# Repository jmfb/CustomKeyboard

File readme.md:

# Custom Keyboards

## V1

I took a prefabricated tenkeyless PCB and used a dremel to cut it into 3 pieces:
- Left hand board (jagged cut at F5, 6, T, G, B)
- Right hand board (jagged cut at F6, 7, Y, H, N)
- Arrow keys

I proceeded to use the dremel to sever all PCB traces for the keys but left the diode traces.
Cherry MX brown switches were then directly mounted to the PCB.  Note that these switches were
the ones designed to be plate mounted (did not include the extra two plastic pegs for direct PCB mounting) so the keys ended up looking crooked.

The switches were then wired into the standard row/column matrix and wires were all routed through to an external Teensy2.0 controller.  2x5 and 2x3 headers were used for the connecting cables.  The keycaps were a standard profile blank set.

The next phase was designing a custom PCB for the number pad (to "complete" the full keyboard) and testing out both 3D printed and lasercut mounting plates.

### Lessons Learned

- Direct PCB mounting was crooked (at least using the non-PCB mount keys).
- Lasercut acrylic mounting plates were sturdier, cheaper, and looked cooler than the 3D printed versions.
- Arrow keys and number pad could be combined into a single board.
- Blank keycaps were difficult to use (I guess I still occasionally look).
- The placement of the right hand spacebar required the right thumb to tuck.
- The external controller for the Teensy and the external cable management boards made for too many components.
- The keys come with holes for LEDs that I might as well be using.
- A wristpad was necessary to use the keyboard and would nice if it were affixed.

## V2

I designed 3 custom PCBs using KiCad:
- Left hand board (capslock key replaced with Teensy2.0 controller)
- Right hand board
- Accessory board (arrows and numbpad)

I designed lasercut mounting plates using OpenSCAD.

I upgraded to using Cherry MX blue switches and double shot DCS keycaps and installed green LEDs on each key.

I extended the base plate to make room to glue wristpads onto the boards.

### Lessons Learned

- Direct soldering of the LEDs to the PCB made it difficult to replace them when they loosened or burned out.
- The double shot keycaps felt great but didn't allow for the LED light to show through.  Translucent keycaps would have been better.
- A better solution than just gluing the PCB to a board would be needed for a case (someting that could be assembled/disassembled, and that had walls).

## V3

This design used the same PCBs and mounting plates as V2.

Cherry MX green switches were used.  After using a sampler board with several types of switches I thought the ultra stiff key would be awesome.

Lasercut faceplates, lasercut baseplates, and 3D printed case walls were designed using OpenSCAD.  Three versions of the case walls were printed to test out different materials and different 3D printing vendors: i.Materialise, Sculpteo, and Shapeways.

SIP LED sockets were put into each of the key switches to allow for the LEDs to be replaced.  A mix of blue and green LEDs were used (blue for control keys).

Doubleshot translucent keycaps were used to allow for the LED light to show through.

The controller logic was updated to make the left hand space be a hyper key.

### Lessons Learned

- The 3D walls designed for the case were too tight of a fit and bowed out.  It made for a sturdy design but required too precise measurements for a perfect fit.  The next case should use screws/standoffs to mount the PCB vs. grooved walls.
- 3D printing was too expensive and slow compared to laser cutting.  The next case should be made solely from lasercut parts.
- The hyper key functionality was great, but I occassionally missed having the left hand spacebar.  More keys next time.
- The 2x5/2x3 connector cables looked unprofessional (probably because of the rainbow colored cables).
- I measured the baseplates based on the previous wristpad size and when I couldn't reorder the same type of wristpad had to use bigger ones that hung over the edge of the baseplates.  Obtain wristpads prior to measuring baseplates.
- The cutoff edge of the wristpads looked unprofessional.
- After double checking the PCB and laser cutting capabilities there is no need to keep the accessory board separate.
- Stabilizers for the 2+ keys would be nice.  Need to update PCB for holes, mounting plates for holes, and move PCB components in the way of the footprints.
- Not sure how I feel about the green switches.  I like the stiff feel but I don't think I love them like I did the blues.
- The LEDs were mounted on the bottom of the keys but the translucent keycaps were designed to shine through the top.  Will need to flip key switches to optimize translucent effects of the keycaps.  Note that vertical keys should have LEDs to the left.
- The key spacing for larger unit keys (1.25, 1.5, 1.75, 2, 2.25, and 2.75) had been using measured positions and worked.  However, when attempting to make a perfect rectangle for each hand it was discovered that 19mm * keysize was needed to prevent 1mm error for several rows.  This increased resolution for key spacing to 1/8th mm from 1/2 mm.

## V4

3 new PCBs were designed using KiCad:
- Extended left hand board (include arrow keys and slightly inverted numpad to mirror right hand board).
- Extended right hand board (combined right hand board and accessory board).
- External connector board (houses Teensy and 2 25-pin D-sub connectors).

The left hand board had arrow keys added to the left of the previous left edge.  A numpad was added to the left of that but with the outside edge of keys mirrored and the zero and period flipped.  The mirroring was so the enter would still be hit with the pinky and the zero still with the thumb.  The numbers were not flipped because I didn't want to retrain my brain for my left hand.  Above the numpad, four programmable buttons were added (N1-4, sometimes used for volume controls or extended operators for the numpad).  To the left of the numpad a vertical row of programmable buttons was added (M1-6, as part of the more keys strategy) that used some of the gaps in the row/column matrix.  To the right of the jagged edge, a vertical row of programmable keys was added (L1-6) and different sized keys were used to make the board a perfect rectangle.  A new hyper key (LEFT_HYPER) was also added to the left of the spacebar to fill in the gap between alt and the spacebar.  The capslock key was re-added since the Teensy is being moved onto its own board (whether this gets remapped is programmable).  The main part of this board is 8.5 standard keys wide.

The right hand board was combined with the previous accessory board.  The same jagged gap was filled on this board to make it a perfect rectangle though one more key was added (two keys were added to the left of the function key row) for an additional 7 keys (R1-7).  A new hyper key was added to the right of the spacebar (RIGHT_HYPER) and the right windows key was re-added (previously just had the right menu key between alt and ctrl).  The same N1-4 and M1-6 keys were also added to this board (note they are not independently programmable because they map to the same row/column scan position).  The main part of this board is 10 standard keys wide.

The full keyboard contains 170 keys; 130 distinct row/column scan positions.  Note that there are still 2 unused row/scan positions in the 12x11 row/scan matrix.  There wasn't anywhere convenient left to put them though.

A single 25-pin D-sub connector exists on each board. 12 row pins, 11 column pins, VCC, and GND (for LEDs).  Instead of chaining the left board to the right board and having the USB cable and connector cable on the left board, the Teensy was moved off onto a controller board.  The controller board just maps the Teensy pins to 2 D-sub connectors (one for the left hand board and one for the right hand board, with both cables having the same pin assignments).

The case design was switched to use all lasercut pieces.  The walls are notched together and slide pegs into the baseplate and faceplate.  A 3mm overhang, 3mm wall depth, and 1mm spacing between wall and PCB makes each dimension of the base/face 14mm longer than the PCB/mounting plate sizes.  Screw holes are drilled into the border and one near the arrow keys for some center support.  M2 screws (5mm male end), 0.5mm washers, 5mm M/F standoffs (3mm wide with 4mm male end), and 8mm F/F standoffs (3mm wide) are used to affix the PCB to the base and affix the faceplate to the walls.  From the bottom, it goes: screw, base, 5mm M/F standoff, PCB, washer, 8mm F/F standoff (though hole for mounting plate), 2 washers, faceplate, washer, screw.

All case parts for all three boards can be combined into a single CAD file and lasercut from two P3 pieces from Ponoko (one for the baseplates and walls and one for the mounting plates and faceplates).  Since there was space for two connector faceplates, I decided to make one with a little bit of artwork and cut out a flux capacitor.  Because if you're going to build your own keyboard why not build one with style!

Cherry PCB mounted stabilizers were added.  Two sets of translucent keycaps were needs due to the number of additional keys.

### Lessons Learned

- D-Sub connector height measurement was imprecise and pushed the faceplate up about 1mm.  Filing it down took part of the edge off, but using a micrometer will yield better wall/faceplate height measurements.
- Using the washers on the screw/standoff connections was impractical due to the small size of the washers, the inconvenient location of the screws (near walls or central to the board and under the mounting plate).  The screw/standoff premise is solid though and made a very sturdy and professional looking case.
- The location of the D-Sub connectors on the boards was inconvenient for placement near monitors.  I think the outside edge would make the most sense for the next version.
- More keys was a bad idea.  The inner row keys ended up getting pressed by accident too often and ruined the tactile feel for finding my position on the keyboard without looking.  While there was potential for adding useful keys (left hand enter, backspace, right hand tab, escape) the opposite was experienced.  The extra left hand board made it difficult to find home for my left hand (naturally always seeking leftmost position).  The extra numpad and outer macro keys filled out the keyboard but were too out of the way to add anything useful to them (it was more burdensome to try to figure out what to assign to the keys).  I am not sure about how I feel about the hyper key near the spacebar because of the other things that made typing difficult.  I do still think a hyperkey or two is a good idea.
- The offboard teensy and extra cabling has the benefit of keeping a single cable going to each board but uncovered a problem with wiring resistance that was solved with a delay in the controller logic during rowscan to allow the signals in the lines to stabilize (which was taking at least one extra clock cycle and causing phantom keypresses in the first two columns of the scan matrix).
- I didn't glue down the wristpad on this one because I was tired of buying more and more wristpads.  However, they slip around too much otherwise.  They need to be fixed to the keyboard case.  Sewing the edge flap down did make them look much better than the glued end of cut off end.
- I think the Cherry MX Green switches were cool for a while but in the end not as nice to type on.  Going back to the blue switches from V2 felt amazingly good by comparison.
- The mix of blue and green LEDs was kind of cool but I don't love it.  I think short of RGB LEDs I will stick with a single color.  Probably green but blue was fine too.  The SIP sockets rock.
- Having the CapsLock key back was a mistake - definitely never use it and every time it is pressed was an accidental hit.  I might leave it off next time.  Would the overall look suffer though?
- The flux capacitor design in the connector board was basically invisible because of the clear faceplate.  However, the top leg did provide a hole through to the teensy reset button which came in handy.  Might just keep that hole.
- The cherry stabilizers worked out great.  Clean fit into PCB, perfect cutout for mounting plate.  There was one resistor that was close to a support bar.
- Pro-tip: prior to soldering the keys onto the PCB make sure all key pins went through.  One pin had bent down and I didn't discover it until half of the keys were soldered.  That meant I was almost fucked.  I ended up shoving a bit of wire through the hole and drenching it in solder hoping that surface tension would pull enough solder down the wire to make the connection to the bent pin.  It worked, but had it not I don't know what I would have done.
- A few more screws in certain locations would make the faceplate more stable (at least on the right hand board).

## V5

### Left Hand

- Getting rid of left hand accessory board (arrows and numpad).
- Getting rid of outside column macro keys (M1-6) and inside column macro keys (L1-6).
- Removing the caps lock key.  Could have left it for looks and mapped it to a hyper key or something, but not worth the mistakes.
- Keeping the left hyper key.
- Moving D-Sub connector to left edge at the top.
- Using a total of 7 screw holes to build case.
- Total of 35 keys (2 2+ keys) with max row width being 7.5 keys (bottom row).

### Right Hand

- Getting rid of outside column macro keys (M1-6) and inside column macro keys (R1-7).
- Keeping numpad macro keys (N1-4).
- Keeping right hyper key and right windows key.
- Moving D-Sub connector to right edge at the top.
- Using a total of 15 screw holes to build case.
- Total of 75 keys (7 2+ keys) with max row width being 9 keys (bottom row, excluding accessory keys).

### Connector Board

- Reusing design from V4.  Will be able to use the same PCB.
- Leaving a hole in the faceplate for the Teensy reset button.
- Using a total of 4 screw holes to build case.

### General Updates

- Fixing case wall height to take into account micrometer measurements for D-Sub connectors (10.3mm vs. previous measurement of 9.5mm).
- Using 10mm F/F standoffs to connect PCB to faceplate (a 0.3mm gap will exist, should be fine).
- Not using washers in any part of screw assembly (too small and can't get in most spots).
- Using same color LED for all keys (green).
- Going back to Cherry MX Blue switches.
- Plan on getting custom DCS row 6 keycaps for hyper keys (left is 1.5, right is 1.75) and space keys (both 2.25).

### Lessons Learned

- This keyboard is just plain awesome.
- Right hand board is still very large and is sometimes awkward to fit onto desk near monitors.
- Large right hand board occasionally gets wobble when crossing desk boundaries.
- Very minor use of hyper keys due to completely normal keyboard layout.
- N1-4 keys are never used (and completely out of the way).
- Uses 3 2.25 keys (left shift and both spacebars) which makes complete keycap sets difficult.
- Using unused capslock as right hyper is perfect.
- Still do not miss the capslock key (nor do I wish there were a key there I could hit).
- Single color keyboard is okay (looks neat but not awesome).  Have built both a green and blue version.
- Ran out of blue switches for second one and used green for function keys - don't even notice because of how rarely they are used.
- D-sub cables give a classic/punk look to the keyboard but are a bit large (bump into monitors still, even on the outside top).
- Cost for materials (case/PCB) is higher than ideal due to large right hand board.
- Connector board is larger than it needs to be.

## Mini V1

### Goals

- Build a miniature keyboard (40%-like) and use hyper-functionality to improve current coding workflows.
- Have an easy to hit underscore (for snake casing, lambdas, garbage identifier prefixes, etc.).
- Reduce PCB/case material costs (just in case I want two of them again!).
- Have smaller and more hidden cables connecting the boards (keep off-board controller for symmetry).
- Columnar layout (will definitely need to re-learn typing).
- Minimal "reach" keys (1 row up, 1 row down, 1 row over to either side).
- Rely on thumb buttons for extra keys (no clue what layout yet).
- RGB LEDs so I can have that awesome feel of dynamic color and responsive changes.

### Parts, Prices, and Datasheets

- Cherry MX Blue RGB PCB Mount Switches (x23 x2)
	- MX1A-EN1B (NOTE: Only wanted MX1A-EN1A, plate mounted, but were constantly out of stock)
	- [Blue Datasheet](https://www.cherrymx.de/_Resources/Persistent/a531cb6598bc849cbcf131fd7a31814282b74545/EN_CHERRY_MX_BLUE.pdf)
	- [Footprint Datasheet](https://cdn.sparkfun.com/datasheets/Components/Switches/MX%20Series.pdf)
	- [LED Cutout Datasheet](https://drive.google.com/file/d/0B5JcED9YINdnNU1qajJmVmtEcUU/view?resourcekey=0-LZfcyjo3jcX8JEKJD6tRKA)
	- [MechanicalKeyboards](https://mechanicalkeyboards.com/shop/index.php?l=product_detail&p=4451)
	- $0.50 / switch @ 100 = $50.00 (bulk discount)
- Pin Receptacle Connector (Maybe, adds height to key and might throw off 3mm spacing between PCB and mounting plate)
	- 0305-2-15-15-47-27-10-0 (ED90333-ND)
	- [Datasheet](https://www.mill-max.com/products/datasheet/pinsrecs/0305-2-15-80-47-80-10-0)
	- [Digikey](https://www.digikey.com/en/products/detail/mill-max-manufacturing-corp/0305-2-15-15-47-27-10-0/1801940)
	- $0.22906 / connector @ 200 = $45.81 (bulk discount, went in on 500 with Greg).
- Keyswitch Diode (x23 x2)
	- 1N4148 (1N4148FS-ND)
	- [Datasheet](https://rocelec.widen.net/view/pdf/bhc41r7lwc/ONSM-S-A0003539415-1.pdf?t.download=true&u=5oefqw)
	- [Digikey](https://www.digikey.com/en/products/detail/on-semiconductor/1N4148/458603?s=N4IgTCBcDaIIwDkAsckA4BiBlAtAgIiALoC%2BQA)
	- $0.01622 / diode @ 1000 = $16.22 (bulk discount)
- RGB LED with IC (x23 x2)
	- APA102C (iPixel LED)
	- [Datasheet](https://cdn.sparkfun.com/datasheets/Components/LED/APA102C.pdf)
	- [Sparkfun](https://www.sparkfun.com/products/16345)
	- $0.379 / LED @ 50 = $18.95
- 9pin Mini-DIM Female Connector, Through Hole, Right Angle (x1 x2 + connector x2)
	- MD-90S (CP-2490-ND)
	- [Datasheet](https://www.cuidevices.com/product/resource/md-s.pdf)
	- [Digikey](https://www.digikey.com/en/products/detail/cui-devices/MD-90S/145320)
	- $2.95 / connector @ 4 = $10.80
- 9pin Mini-DIM Male/Make 3ft. Cable (x2)
	- MD9MM3BLK
	- [Datasheet](https://www.kraydad.com/mini-din-9-pin-b-type-cables/)
	- [Kraydad](https://www.kraydad.com/mini-din-9-pin-b-type-3-ft-male-to-male-black-cable/)
	- $12.49 / cable @ 2 = $24.98
- Cherry PCB Snap-in Stabilizers (2u x2 x2)
	- 60%/TKL (NOTE: includes 5 2u wires, only need 4)
	- [Amazon](https://www.amazon.com/Genuine-Cherry-PCB-Snap-Stabilizers/dp/B085T8QZJC)
	- $14.99 / pack @ 1 = $14.99
- M4 Hex Brass F/M Standoff 18mm/6mm w/ Screw and Nut (x4 x2)
	- Set of 20 (need 4 or 5 per board)
	- [Amazon](https://www.amazon.com/gp/product/B08ZXSR7MP)
	- $0.5745 / set @ 20 = $11.49
- M4 Brass Washer 9mm OD, 4.3mm ID, 0.8mm Thick (x4 x2)
	- Pack of 100 (need 4 or 5 per board)
	- [Amazon](https://www.amazon.com/gp/product/B009OK2KPU)
	- $0.0827 / washer @ 100 = $8.27
- M2 Brass F/M Standoff 5mm/4mm
	- Pack of 100 (need 4 for controller)
	- [Amazon](https://www.amazon.com/gp/product/B00REFG0TE/ref=ppx_yo_dt_b_search_asin_title?ie=UTF8&psc=1)
	- $0.0949 / standoff @ 100 = $9.49
- M2 Brass F/F Standoff 8mm (first controller)
	- Pack of 50 (need 4 for controller)
	- [Amazon](https://www.amazon.com/gp/product/B00BWLQYRY/ref=ppx_yo_dt_b_search_asin_title?ie=UTF8&psc=1)
	- $0.226 / standoff @ 50 = $11.30
- M2 Brass F/F Standoff 10mm (second controller)
	- Pack of 100 (need 4 for controller)
	- [Rakuten](https://www.rakuten.com/shop/unique-bargains/product/a14081400ux0120/)
	- $0.0683 / standoff @ 100 = $6.83
- M2 5mm Screws
	- Pack of 60 (need 8 for controller)
	- [Amazon](https://www.amazon.com/gp/product/B013T1U4LG/ref=ppx_yo_dt_b_search_asin_title?ie=UTF8&psc=1)
	- $0.1195 / screw @ 60 = $7.17
- Clear Soft Close Drawer Cabinet Door Bumpers (x6 x2 + connector x4)
	- 9.5mm x 3.8mm, 72pc sheet
	- [Amazon](https://www.amazon.com/dp/B06XCGM8JT)
	- $0.0968 / bumper @ 72 = $6.97
- Mini USB A to Mini-B Cable, Black, 3ft (x1)
	- 103896 (any Mini USB cable will do if you already have one)
	- [Amazon](https://www.amazon.com/Monoprice-3-Feet-mini-B-28AWG-103896/dp/B003L18SHC)
	- $5.23 / cable @ 1 = $5.23
- Teensy 2.0 (x1)
	- No pins
	- [Datasheet](https://www.pjrc.com/store/teensy.html)
	- [Amazon](https://www.amazon.com/gp/product/B00NC43256)
	- $18.75 / chip @ 1 = $18.75 ($16 from PJRC but with shipping)
	- NOTE: Plans to discontinue this model in 2022; recommend switching to 32-bit boards.
- Header Pins (x12 x2, though more pins available on Teensy)
	- Breakaway header, straight, brass
	- [Sparkfun](https://www.sparkfun.com/products/116)
	- $1.50 / 40pin strip @ 1 = $1.50
	- NOTE: Larger volumes and lower per-pin cost are on amazon but not brass pins
- Demultiplexer, 3:8 (x1 x2)
	- SN74HC138N (296-1575-5-ND)
	- [Datasheet](https://www.ti.com/lit/ds/scls107f/scls107f.pdf)
	- [Digikey](https://www.digikey.com/en/products/detail/texas-instruments/SN74HC138N/277221)
	- $0.461 / chip @ 10 = $4.61 (bulk discount)
- Parallel Load, Shift Register (x1 x2)
	- SN74HC165N (296-8251-5-ND)
	- [Datasheet](https://www.ti.com/lit/ds/symlink/sn74hc165.pdf)
	- [Digikey](https://www.digikey.com/en/products/detail/texas-instruments/SN74HC165N/376966)
	- $0.525 / chip @ 10 = $5.25 (bulk discount)
- 10kOhm Pullup Resistors (x8 x2)
	- CF18JT10K0 (CF18JT10K0CT-ND - Cut Tape (CT))
	- [Datasheet](https://www.seielect.com/catalog/sei-cf_cfm.pdf)
	- [Digikey](https://www.digikey.com/en/products/detail/stackpole-electronics-inc/CF18JT10K0/1741566)
	- $0.01116 / resistor @ 500 = $5.58 (bulk discount)
- Wristpad (x1 x2, but both cut from 1)
	- Glorious Gaming Write Pad, Standard Size
	- [Amazon](https://www.amazon.com/Glorious-Gaming-Wrist-Pad-Rest/dp/B00V5AXPTW)
	- $26.99 / pad @ 1 = $26.99
- Doubleshot Translucent Pudding Keycaps (x15 x2)
	- Standard Set
	- [Amazon](https://www.amazon.com/gp/product/B09241HV9H)
	- $19.99 / set @ 1 = $19.99
- DCS Clear Keycaps (x8 x2)
	- 1u R2 x2, 1u R3 x2, 1u R4 x8, 2u R3/4 x4
	- [Datasheet](https://pimpmykeyboard.com/template/images/DCSFamily.pdf)
	- [PimpMyKeyboard](https://pimpmykeyboard.com/dcs-clear-keys-and-key-sets/)
	- $1.00 / 1u @ 12 = $12.00
	- $1.50 / 2u @ 4 = $6.00
- Laser Cut Parts
	- [Ponoko](https://www.ponoko.com)
	- All 3mm parts are Green Translucent Acrylic
	- All 1.5mm parts are Clear Acrylic (not available in Green Translucent)
	- Controller (3mm) $7.69 @ 1 = $7.69
	- Base Plate (3mm) $7.15 @ 2 = $14.30
	- Mounting Plate (1.5mm) $7.71 @ 2 = $15.42
	- Lower Layer (3mm) $5.965 @ 4 = $23.86
	- Upper Layer (3mm) $6.08 @ 2 = $12.16
	- Face Plate (3mm) $3.855 @ 4 = $15.42
	- Face Plate (1.5mm) $2.815 @ 2 = $5.63
	- Multi-product discount $30.91
	- Setup Fee $14.00
	- Total: $77.57
- PCB
	- [Seeed Studio](https://www.seeedstudio.com)
	- Controller $0.98 @ 5 = $4.90
	- Left Hand $6.486 @ 5 = $32.43
	- Right Hand $6.486 @ 5 = $32.43
	- Shipping (DHL from China) $30.19
	- Total: $19.99 @ 5 = $99.95
- Total cost of parts for a single keyboard: $313.34

### Lessons Learned

- Fitting 5x5mm LEDs not a perfect fit (could have made a tad wider for flush fit; would also fit rounded PCB cut corner issue too)
- Soldering LEDs difficult.  Not sure what to do about this other than magnifying glass w/ light.
- Chaining VCC/GND may have been a poor choice, still not sure.  Definitely problematic when attempting to remove an LED.
- Socketing switches seems like a good idea (reduce switch cost for multiple prototypes, allow replacing switches in long-lived versions).  However, increases distance between mounting plate and PCB by ~1mm.  I think I can take that out on pegs.
- With the surface mount pegs, the mounting plate does seem a little bit redundant.  Eliminating the mounting plate and the 1.5mm faceplate layer would reduce overall height by 3mm (shorter M4 scews) and allow for a completely 3mm layer construction.
- Controller board; teensy height from PCB is slightly greater than the 8mm F/F standoffs (not sure how I missed that).  Damn, old controller used 10mm F/F standoff.
- Well, it puts the previous lessons to shame, but the controller "lid" didn't go deep enough with the connector cutouts!  Missed "PCB spacing, wall depth, overhang" padding and just did connector size.
- Tab being lower for the pinky takes getting used to (hit escape a lot).
- Only using bottom half of 2-keys.  Possibly simplify down to 1u size?
- Sometimes hit Win instead of Ctrl when reaching with thumb.  Could stagger keys for thumb; possibly get rid of one of grid keys and just have left hand Win and right hand Menu (or no Menu, I mean who uses that key?)
- Had a few iterations of controller software.  Unit tests for expected key reports were vital (lots of bugs found that way and prevent breaking changes in the future).

## Mini V2

### Goals

- Fix LED hole size to make assembly and soldering easier.
	- Move cutout to keyswitch footprint (manually in file if IDE does not support it).
	- Increase width of cutout to allow surface mount leads to fit inside PCB.
	- Also increase width of peg cutout to account for rounded PCB cutout.
- Fix all incorrect case measurements.
	- 10mm standoffs for controller top.
	- Fix controller lid cutouts for connectors.
	- Reduce peg inner height by 1mm to account for keyswitch sockets.
	- Adjust connector cutout (rubs on bottom).
	- Add holes for demux and register to mounting plate.
- Add hardware support for right or left hand detection.
	- Hardwire first two register pins to 01 for left and 10 for right.  11 indicates disconnected.
	- Software detection to read keyscan and switch LED output.

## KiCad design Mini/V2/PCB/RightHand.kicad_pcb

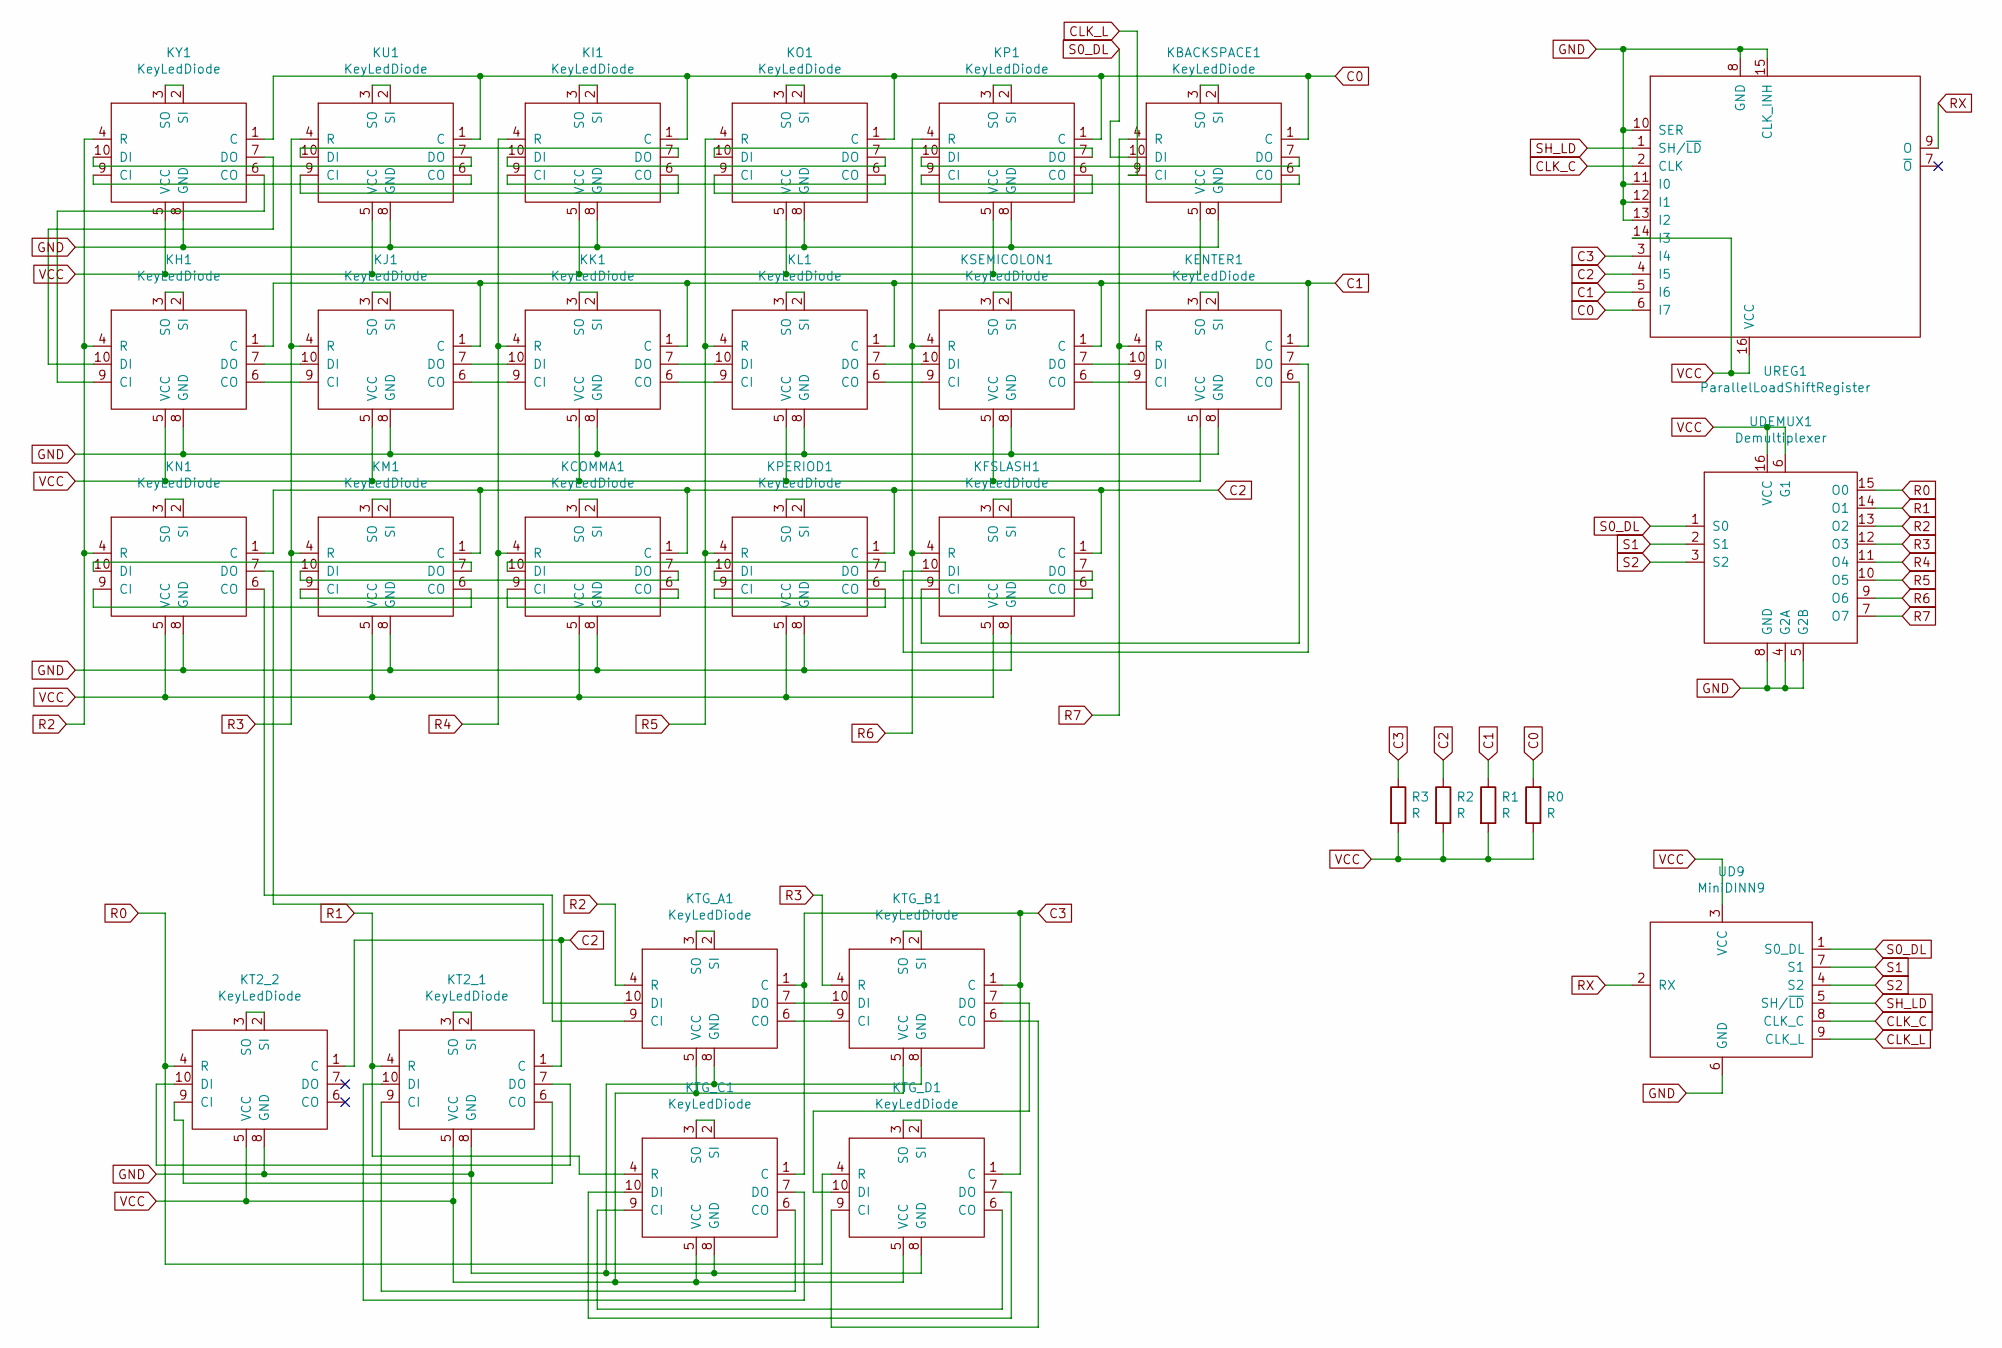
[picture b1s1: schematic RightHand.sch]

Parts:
KBACKSPACE1: KeyLedDiode; KeyLedDiodeR2L
KCOMMA1: KeyLedDiode; KeyLedDiodeR2L
KENTER1: KeyLedDiode; KeyLedDiodeL2R
KFSLASH1: KeyLedDiode; KeyLedDiodeR2L
KH1: KeyLedDiode; KeyLedDiodeL2R
KI1: KeyLedDiode; KeyLedDiodeR2L
KJ1: KeyLedDiode; KeyLedDiodeL2R
KK1: KeyLedDiode; KeyLedDiodeL2R
KL1: KeyLedDiode; KeyLedDiodeL2R
KM1: KeyLedDiode; KeyLedDiodeR2L
KN1: KeyLedDiode; KeyLedDiodeR2L
KO1: KeyLedDiode; KeyLedDiodeR2L
KP1: KeyLedDiode; KeyLedDiodeR2L
KPERIOD1: KeyLedDiode; KeyLedDiodeR2L
KSEMICOLON1: KeyLedDiode; KeyLedDiodeL2R
KT2_1: KeyLedDiode; Key2LedDiodeL2R
KT2_2: KeyLedDiode; Key2LedDiodeR2L
KTG_A1: KeyLedDiode; KeyLedDiodeL2R
KTG_B1: KeyLedDiode; KeyLedDiodeL2R
KTG_C1: KeyLedDiode; KeyLedDiodeR2L
KTG_D1: KeyLedDiode; KeyLedDiodeR2L
KU1: KeyLedDiode; KeyLedDiodeR2L
KY1: KeyLedDiode; KeyLedDiodeR2L
R0, R1, R2, R3: R; PullupResistor
UD9: MiniDINN9; MiniDin9
UDEMUX1: Demultiplexer; DualInlineMicrochip2x8
UREG1: ParallelLoadShiftRegister; DualInlineMicrochip2x8

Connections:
C0: KBACKSPACE1.1 (C), KI1.1 (C), KO1.1 (C), KP1.1 (C), KU1.1 (C), KY1.1 (C), R0.2, UREG1.6 (I7)
C1: KENTER1.1 (C), KH1.1 (C), KJ1.1 (C), KK1.1 (C), KL1.1 (C), KSEMICOLON1.1 (C), R1.1, UREG1.5 (I6)
C2: KCOMMA1.1 (C), KFSLASH1.1 (C), KM1.1 (C), KN1.1 (C), KPERIOD1.1 (C), KT2_1.1 (C), KT2_2.1 (C), R2.1, UREG1.4 (I5)
C3: KTG_A1.1 (C), KTG_B1.1 (C), KTG_C1.1 (C), KTG_D1.1 (C), R3.1, UREG1.3 (I4)
CLK_C: UD9.8 (CLK_C), UREG1.2 (CLK)
CLK_L: KBACKSPACE1.9 (CI), UD9.9 (CLK_L)
GND: KBACKSPACE1.8 (GND), KCOMMA1.8 (GND), KENTER1.8 (GND), KFSLASH1.8 (GND), KH1.8 (GND), KI1.8 (GND), KJ1.8 (GND), KK1.8 (GND), KL1.8 (GND), KM1.8 (GND), KN1.8 (GND), KO1.8 (GND), KP1.8 (GND), KPERIOD1.8 (GND), KSEMICOLON1.8 (GND), KT2_1.8 (GND), KT2_2.8 (GND), KTG_A1.8 (GND), KTG_B1.8 (GND), KTG_C1.8 (GND), KTG_D1.8 (GND), KU1.8 (GND), KY1.8 (GND), UD9.6 (GND), UDEMUX1.4 (G2A), UDEMUX1.5 (G2B), UDEMUX1.8 (GND), UREG1.8 (GND), UREG1.10 (SER), UREG1.11 (I0), UREG1.12 (I1), UREG1.13 (I2), UREG1.15 (CLK_INH)
unnamed: KBACKSPACE1.2 (SI), KBACKSPACE1.3 (SO)
unnamed: KBACKSPACE1.6 (CO), KP1.9 (CI)
unnamed: KBACKSPACE1.7 (DO), KP1.10 (DI)
unnamed: KCOMMA1.2 (SI), KCOMMA1.3 (SO)
unnamed: KCOMMA1.6 (CO), KM1.9 (CI)
unnamed: KCOMMA1.7 (DO), KM1.10 (DI)
unnamed: KCOMMA1.9 (CI), KPERIOD1.6 (CO)
unnamed: KCOMMA1.10 (DI), KPERIOD1.7 (DO)
unnamed: KENTER1.2 (SI), KENTER1.3 (SO)
unnamed: KENTER1.6 (CO), KFSLASH1.9 (CI)
unnamed: KENTER1.7 (DO), KFSLASH1.10 (DI)
unnamed: KENTER1.9 (CI), KSEMICOLON1.6 (CO)
unnamed: KENTER1.10 (DI), KSEMICOLON1.7 (DO)
unnamed: KFSLASH1.2 (SI), KFSLASH1.3 (SO)
unnamed: KFSLASH1.6 (CO), KPERIOD1.9 (CI)
unnamed: KFSLASH1.7 (DO), KPERIOD1.10 (DI)
unnamed: KH1.2 (SI), KH1.3 (SO)
unnamed: KH1.6 (CO), KJ1.9 (CI)
unnamed: KH1.7 (DO), KJ1.10 (DI)
unnamed: KH1.9 (CI), KY1.6 (CO)
unnamed: KH1.10 (DI), KY1.7 (DO)
unnamed: KI1.2 (SI), KI1.3 (SO)
unnamed: KI1.6 (CO), KU1.9 (CI)
unnamed: KI1.7 (DO), KU1.10 (DI)
unnamed: KI1.9 (CI), KO1.6 (CO)
unnamed: KI1.10 (DI), KO1.7 (DO)
unnamed: KJ1.2 (SI), KJ1.3 (SO)
unnamed: KJ1.6 (CO), KK1.9 (CI)
unnamed: KJ1.7 (DO), KK1.10 (DI)
unnamed: KK1.2 (SI), KK1.3 (SO)
unnamed: KK1.6 (CO), KL1.9 (CI)
unnamed: KK1.7 (DO), KL1.10 (DI)
unnamed: KL1.2 (SI), KL1.3 (SO)
unnamed: KL1.6 (CO), KSEMICOLON1.9 (CI)
unnamed: KL1.7 (DO), KSEMICOLON1.10 (DI)
unnamed: KM1.2 (SI), KM1.3 (SO)
unnamed: KM1.6 (CO), KN1.9 (CI)
unnamed: KM1.7 (DO), KN1.10 (DI)
unnamed: KN1.2 (SI), KN1.3 (SO)
unnamed: KN1.6 (CO), KTG_A1.9 (CI)
unnamed: KN1.7 (DO), KTG_A1.10 (DI)
unnamed: KO1.2 (SI), KO1.3 (SO)
unnamed: KO1.9 (CI), KP1.6 (CO)
unnamed: KO1.10 (DI), KP1.7 (DO)
unnamed: KP1.2 (SI), KP1.3 (SO)
unnamed: KPERIOD1.2 (SI), KPERIOD1.3 (SO)
unnamed: KSEMICOLON1.2 (SI), KSEMICOLON1.3 (SO)
unnamed: KT2_1.2 (SI), KT2_1.3 (SO)
unnamed: KT2_1.6 (CO), KT2_2.9 (CI)
unnamed: KT2_1.7 (DO), KT2_2.10 (DI)
unnamed: KT2_1.9 (CI), KTG_C1.6 (CO)
unnamed: KT2_1.10 (DI), KTG_C1.7 (DO)
unnamed: KT2_2.2 (SI), KT2_2.3 (SO)
unnamed: KTG_A1.2 (SI), KTG_A1.3 (SO)
unnamed: KTG_A1.6 (CO), KTG_B1.9 (CI)
unnamed: KTG_A1.7 (DO), KTG_B1.10 (DI)
unnamed: KTG_B1.2 (SI), KTG_B1.3 (SO)
unnamed: KTG_B1.6 (CO), KTG_D1.9 (CI)
unnamed: KTG_B1.7 (DO), KTG_D1.10 (DI)
unnamed: KTG_C1.2 (SI), KTG_C1.3 (SO)
unnamed: KTG_C1.9 (CI), KTG_D1.6 (CO)
unnamed: KTG_C1.10 (DI), KTG_D1.7 (DO)
unnamed: KTG_D1.2 (SI), KTG_D1.3 (SO)
unnamed: KU1.2 (SI), KU1.3 (SO)
unnamed: KU1.6 (CO), KY1.9 (CI)
unnamed: KU1.7 (DO), KY1.10 (DI)
unnamed: KY1.2 (SI), KY1.3 (SO)
R0: KT2_2.4 (R), KTG_D1.4 (R), UDEMUX1.15 (O0)
R1: KT2_1.4 (R), KTG_C1.4 (R), UDEMUX1.14 (O1)
R2: KH1.4 (R), KN1.4 (R), KTG_A1.4 (R), KY1.4 (R), UDEMUX1.13 (O2)
R3: KJ1.4 (R), KM1.4 (R), KTG_B1.4 (R), KU1.4 (R), UDEMUX1.12 (O3)
R4: KCOMMA1.4 (R), KI1.4 (R), KK1.4 (R), UDEMUX1.11 (O4)
R5: KL1.4 (R), KO1.4 (R), KPERIOD1.4 (R), UDEMUX1.10 (O5)
R6: KFSLASH1.4 (R), KP1.4 (R), KSEMICOLON1.4 (R), UDEMUX1.9 (O6)
R7: KBACKSPACE1.4 (R), KENTER1.4 (R), UDEMUX1.7 (O7)
RX: UD9.2 (RX), UREG1.9 (O)
S0_DL: KBACKSPACE1.10 (DI), UD9.1 (S0_DL), UDEMUX1.1 (S0)
S1: UD9.7 (S1), UDEMUX1.2 (S1)
S2: UD9.4 (S2), UDEMUX1.3 (S2)
SH_LD: UD9.5 (SH/~LD), UREG1.1 (SH/~LD)
VCC: KBACKSPACE1.5 (VCC), KCOMMA1.5 (VCC), KENTER1.5 (VCC), KFSLASH1.5 (VCC), KH1.5 (VCC), KI1.5 (VCC), KJ1.5 (VCC), KK1.5 (VCC), KL1.5 (VCC), KM1.5 (VCC), KN1.5 (VCC), KO1.5 (VCC), KP1.5 (VCC), KPERIOD1.5 (VCC), KSEMICOLON1.5 (VCC), KT2_1.5 (VCC), KT2_2.5 (VCC), KTG_A1.5 (VCC), KTG_B1.5 (VCC), KTG_C1.5 (VCC), KTG_D1.5 (VCC), KU1.5 (VCC), KY1.5 (VCC), R0.1, R1.2, R2.2, R3.2, UD9.3 (VCC), UDEMUX1.6 (G1), UDEMUX1.16 (VCC), UREG1.14 (I3), UREG1.16 (VCC)

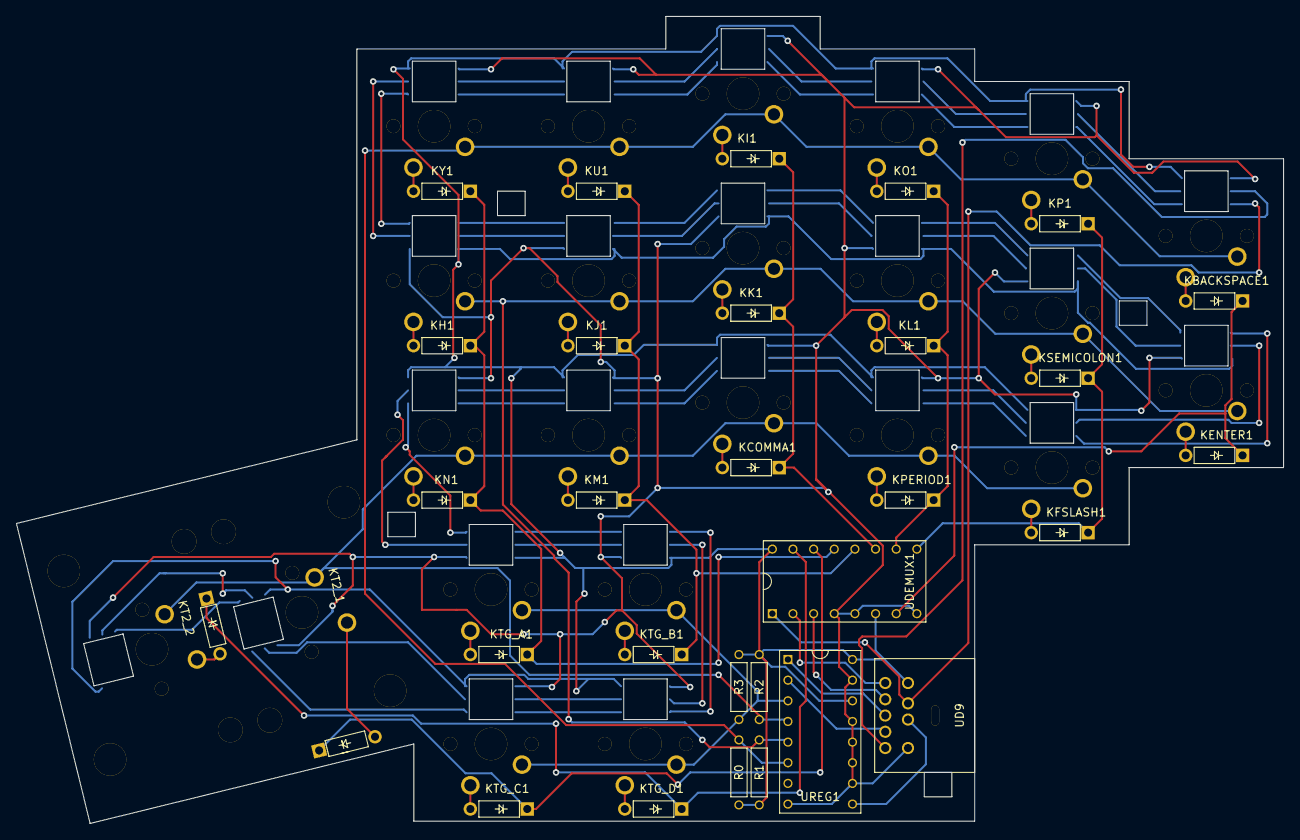
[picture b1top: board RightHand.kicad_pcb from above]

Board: 2 copper layers, 155.9 x 99.3 mm, 30 parts (0 on the bottom side), 88 nets.

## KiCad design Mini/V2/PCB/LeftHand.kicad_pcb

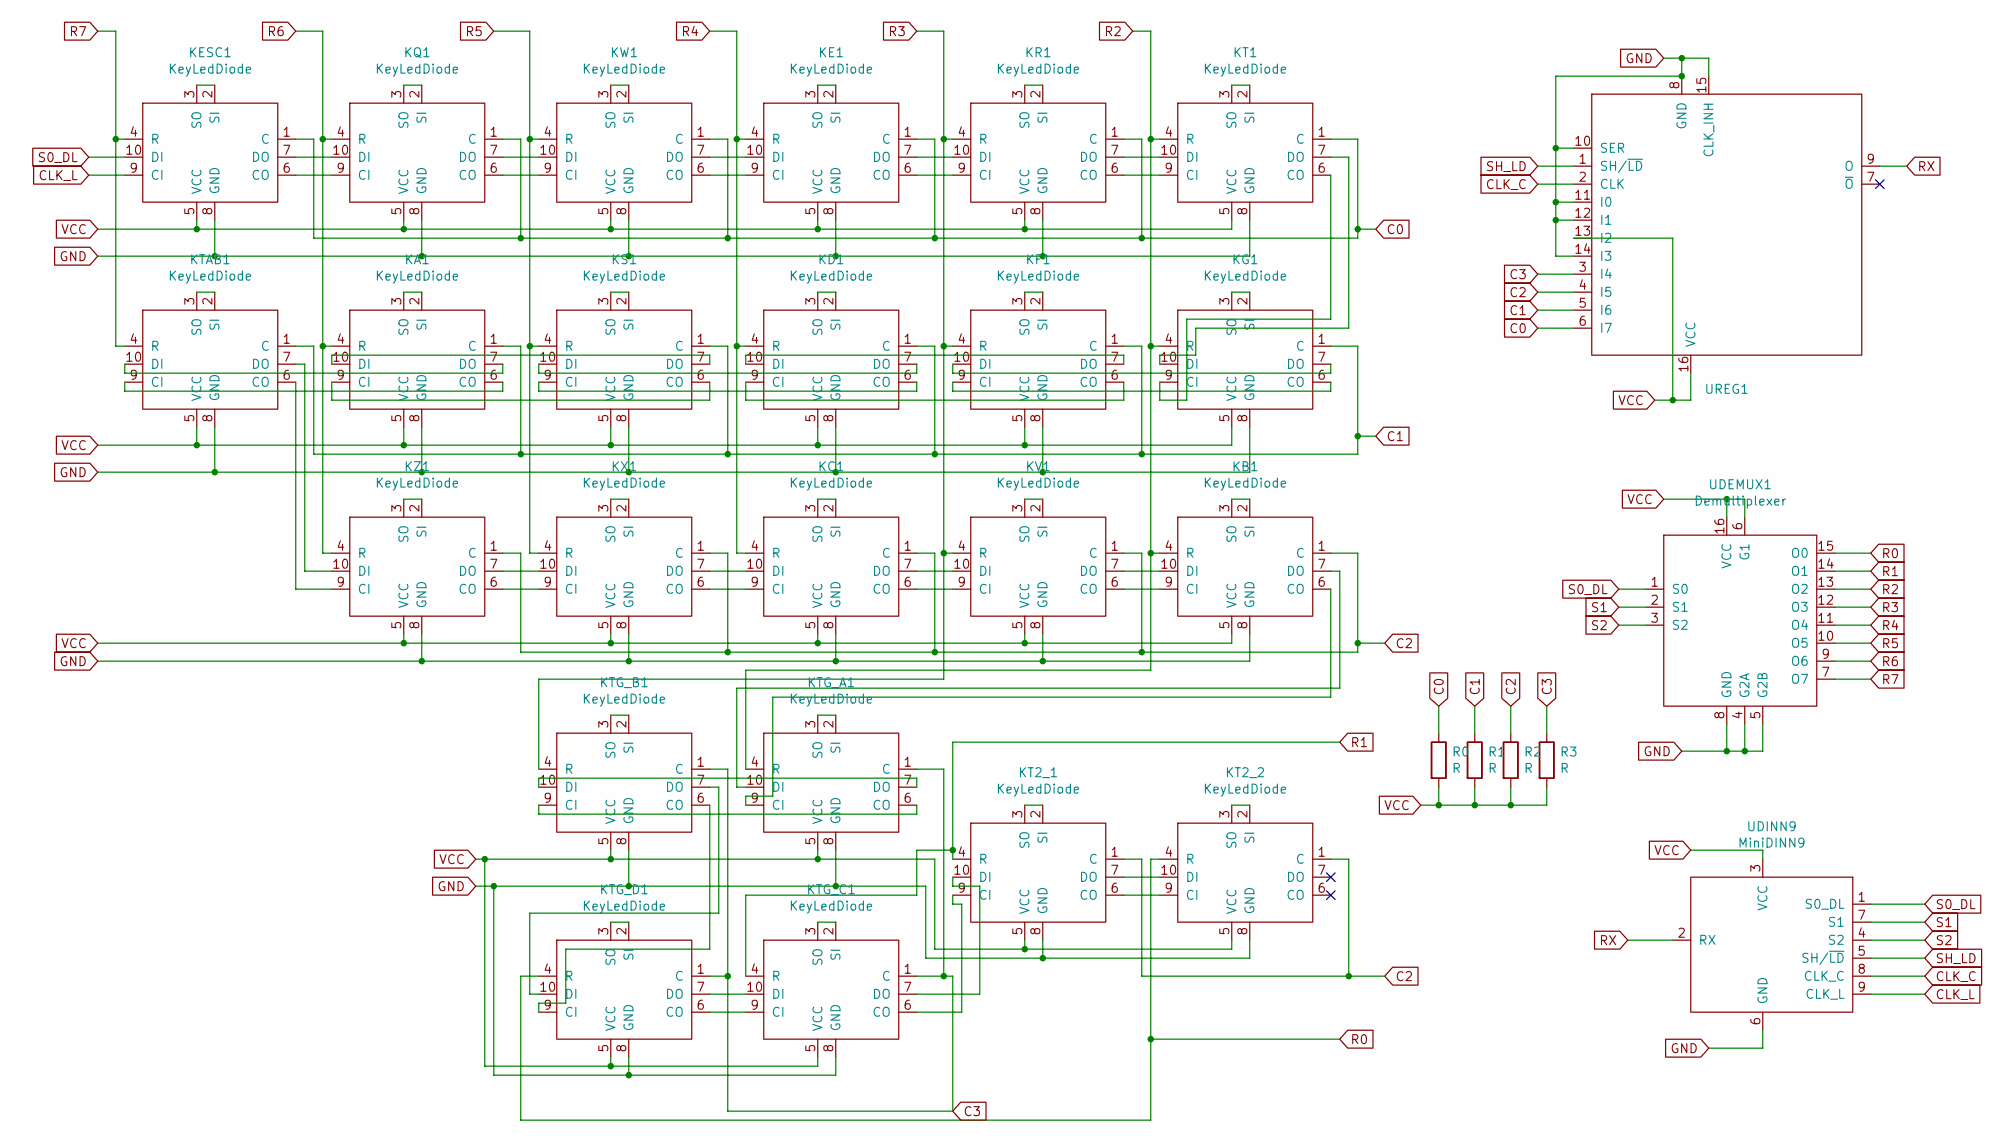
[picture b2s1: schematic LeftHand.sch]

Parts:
KA1: KeyLedDiode; KeyLedDiodeR2L
KB1: KeyLedDiode; KeyLedDiodeL2R
KC1: KeyLedDiode; KeyLedDiodeL2R
KD1: KeyLedDiode; KeyLedDiodeR2L
KE1: KeyLedDiode; KeyLedDiodeL2R
KESC1: KeyLedDiode; KeyLedDiodeL2R
KF1: KeyLedDiode; KeyLedDiodeR2L
KG1: KeyLedDiode; KeyLedDiodeR2L
KQ1: KeyLedDiode; KeyLedDiodeL2R
KR1: KeyLedDiode; KeyLedDiodeL2R
KS1: KeyLedDiode; KeyLedDiodeR2L
KT1: KeyLedDiode; KeyLedDiodeL2R
KT2_1: KeyLedDiode; Key2LedDiodeL2R
KT2_2: KeyLedDiode; Key2LedDiodeR2L
KTAB1: KeyLedDiode; KeyLedDiodeR2L
KTG_A1: KeyLedDiode; KeyLedDiodeR2L
KTG_B1: KeyLedDiode; KeyLedDiodeR2L
KTG_C1: KeyLedDiode; KeyLedDiodeL2R
KTG_D1: KeyLedDiode; KeyLedDiodeL2R
KV1: KeyLedDiode; KeyLedDiodeL2R
KW1: KeyLedDiode; KeyLedDiodeL2R
KX1: KeyLedDiode; KeyLedDiodeL2R
KZ1: KeyLedDiode; KeyLedDiodeL2R
R0, R1, R2, R3: R; PullupResistor
UDEMUX1: Demultiplexer; DualInlineMicrochip2x8
UDINN9: MiniDINN9; MiniDin9
UREG1: ParallelLoadShiftRegister; DualInlineMicrochip2x8

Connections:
C0: KE1.1 (C), KESC1.1 (C), KQ1.1 (C), KR1.1 (C), KT1.1 (C), KW1.1 (C), R0.1, UREG1.6 (I7)
C1: KA1.1 (C), KD1.1 (C), KF1.1 (C), KG1.1 (C), KS1.1 (C), KTAB1.1 (C), R1.1, UREG1.5 (I6)
C2: KB1.1 (C), KC1.1 (C), KT2_1.1 (C), KT2_2.1 (C), KV1.1 (C), KX1.1 (C), KZ1.1 (C), R2.1, UREG1.4 (I5)
C3: KTG_A1.1 (C), KTG_B1.1 (C), KTG_C1.1 (C), KTG_D1.1 (C), R3.1, UREG1.3 (I4)
CLK_C: UDINN9.8 (CLK_C), UREG1.2 (CLK)
CLK_L: KESC1.9 (CI), UDINN9.9 (CLK_L)
GND: KA1.8 (GND), KB1.8 (GND), KC1.8 (GND), KD1.8 (GND), KE1.8 (GND), KESC1.8 (GND), KF1.8 (GND), KG1.8 (GND), KQ1.8 (GND), KR1.8 (GND), KS1.8 (GND), KT1.8 (GND), KT2_1.8 (GND), KT2_2.8 (GND), KTAB1.8 (GND), KTG_A1.8 (GND), KTG_B1.8 (GND), KTG_C1.8 (GND), KTG_D1.8 (GND), KV1.8 (GND), KW1.8 (GND), KX1.8 (GND), KZ1.8 (GND), UDEMUX1.4 (G2A), UDEMUX1.5 (G2B), UDEMUX1.8 (GND), UDINN9.6 (GND), UREG1.8 (GND), UREG1.10 (SER), UREG1.11 (I0), UREG1.12 (I1), UREG1.14 (I3), UREG1.15 (CLK_INH)
unnamed: KA1.2 (SI), KA1.3 (SO)
unnamed: KA1.6 (CO), KTAB1.9 (CI)
unnamed: KA1.7 (DO), KTAB1.10 (DI)
unnamed: KA1.9 (CI), KS1.6 (CO)
unnamed: KA1.10 (DI), KS1.7 (DO)
unnamed: KB1.2 (SI), KB1.3 (SO)
unnamed: KB1.6 (CO), KTG_A1.9 (CI)
unnamed: KB1.7 (DO), KTG_A1.10 (DI)
unnamed: KB1.9 (CI), KV1.6 (CO)
unnamed: KB1.10 (DI), KV1.7 (DO)
unnamed: KC1.2 (SI), KC1.3 (SO)
unnamed: KC1.6 (CO), KV1.9 (CI)
unnamed: KC1.7 (DO), KV1.10 (DI)
unnamed: KC1.9 (CI), KX1.6 (CO)
unnamed: KC1.10 (DI), KX1.7 (DO)
unnamed: KD1.2 (SI), KD1.3 (SO)
unnamed: KD1.6 (CO), KS1.9 (CI)
unnamed: KD1.7 (DO), KS1.10 (DI)
unnamed: KD1.9 (CI), KF1.6 (CO)
unnamed: KD1.10 (DI), KF1.7 (DO)
unnamed: KE1.2 (SI), KE1.3 (SO)
unnamed: KE1.6 (CO), KR1.9 (CI)
unnamed: KE1.7 (DO), KR1.10 (DI)
unnamed: KE1.9 (CI), KW1.6 (CO)
unnamed: KE1.10 (DI), KW1.7 (DO)
unnamed: KESC1.2 (SI), KESC1.3 (SO)
unnamed: KESC1.6 (CO), KQ1.9 (CI)
unnamed: KESC1.7 (DO), KQ1.10 (DI)
unnamed: KF1.2 (SI), KF1.3 (SO)
unnamed: KF1.9 (CI), KG1.6 (CO)
unnamed: KF1.10 (DI), KG1.7 (DO)
unnamed: KG1.2 (SI), KG1.3 (SO)
unnamed: KG1.9 (CI), KT1.6 (CO)
unnamed: KG1.10 (DI), KT1.7 (DO)
unnamed: KQ1.2 (SI), KQ1.3 (SO)
unnamed: KQ1.6 (CO), KW1.9 (CI)
unnamed: KQ1.7 (DO), KW1.10 (DI)
unnamed: KR1.2 (SI), KR1.3 (SO)
unnamed: KR1.6 (CO), KT1.9 (CI)
unnamed: KR1.7 (DO), KT1.10 (DI)
unnamed: KS1.2 (SI), KS1.3 (SO)
unnamed: KT1.2 (SI), KT1.3 (SO)
unnamed: KT2_1.2 (SI), KT2_1.3 (SO)
unnamed: KT2_1.6 (CO), KT2_2.9 (CI)
unnamed: KT2_1.7 (DO), KT2_2.10 (DI)
unnamed: KT2_1.9 (CI), KTG_C1.6 (CO)
unnamed: KT2_1.10 (DI), KTG_C1.7 (DO)
unnamed: KT2_2.2 (SI), KT2_2.3 (SO)
unnamed: KTAB1.2 (SI), KTAB1.3 (SO)
unnamed: KTAB1.6 (CO), KZ1.9 (CI)
unnamed: KTAB1.7 (DO), KZ1.10 (DI)
unnamed: KTG_A1.2 (SI), KTG_A1.3 (SO)
unnamed: KTG_A1.6 (CO), KTG_B1.9 (CI)
unnamed: KTG_A1.7 (DO), KTG_B1.10 (DI)
unnamed: KTG_B1.2 (SI), KTG_B1.3 (SO)
unnamed: KTG_B1.6 (CO), KTG_D1.9 (CI)
unnamed: KTG_B1.7 (DO), KTG_D1.10 (DI)
unnamed: KTG_C1.2 (SI), KTG_C1.3 (SO)
unnamed: KTG_C1.9 (CI), KTG_D1.6 (CO)
unnamed: KTG_C1.10 (DI), KTG_D1.7 (DO)
unnamed: KTG_D1.2 (SI), KTG_D1.3 (SO)
unnamed: KV1.2 (SI), KV1.3 (SO)
unnamed: KW1.2 (SI), KW1.3 (SO)
unnamed: KX1.2 (SI), KX1.3 (SO)
unnamed: KX1.9 (CI), KZ1.6 (CO)
unnamed: KX1.10 (DI), KZ1.7 (DO)
unnamed: KZ1.2 (SI), KZ1.3 (SO)
R0: KT2_2.4 (R), KTG_D1.4 (R), UDEMUX1.15 (O0)
R1: KT2_1.4 (R), KTG_C1.4 (R), UDEMUX1.14 (O1)
R2: KB1.4 (R), KG1.4 (R), KT1.4 (R), KTG_A1.4 (R), UDEMUX1.13 (O2)
R3: KF1.4 (R), KR1.4 (R), KTG_B1.4 (R), KV1.4 (R), UDEMUX1.12 (O3)
R4: KC1.4 (R), KD1.4 (R), KE1.4 (R), UDEMUX1.11 (O4)
R5: KS1.4 (R), KW1.4 (R), KX1.4 (R), UDEMUX1.10 (O5)
R6: KA1.4 (R), KQ1.4 (R), KZ1.4 (R), UDEMUX1.9 (O6)
R7: KESC1.4 (R), KTAB1.4 (R), UDEMUX1.7 (O7)
RX: UDINN9.2 (RX), UREG1.9 (O)
S0_DL: KESC1.10 (DI), UDEMUX1.1 (S0), UDINN9.1 (S0_DL)
S1: UDEMUX1.2 (S1), UDINN9.7 (S1)
S2: UDEMUX1.3 (S2), UDINN9.4 (S2)
SH_LD: UDINN9.5 (SH/~LD), UREG1.1 (SH/~LD)
VCC: KA1.5 (VCC), KB1.5 (VCC), KC1.5 (VCC), KD1.5 (VCC), KE1.5 (VCC), KESC1.5 (VCC), KF1.5 (VCC), KG1.5 (VCC), KQ1.5 (VCC), KR1.5 (VCC), KS1.5 (VCC), KT1.5 (VCC), KT2_1.5 (VCC), KT2_2.5 (VCC), KTAB1.5 (VCC), KTG_A1.5 (VCC), KTG_B1.5 (VCC), KTG_C1.5 (VCC), KTG_D1.5 (VCC), KV1.5 (VCC), KW1.5 (VCC), KX1.5 (VCC), KZ1.5 (VCC), R0.2, R1.2, R2.2, R3.2, UDEMUX1.6 (G1), UDEMUX1.16 (VCC), UDINN9.3 (VCC), UREG1.13 (I2), UREG1.16 (VCC)

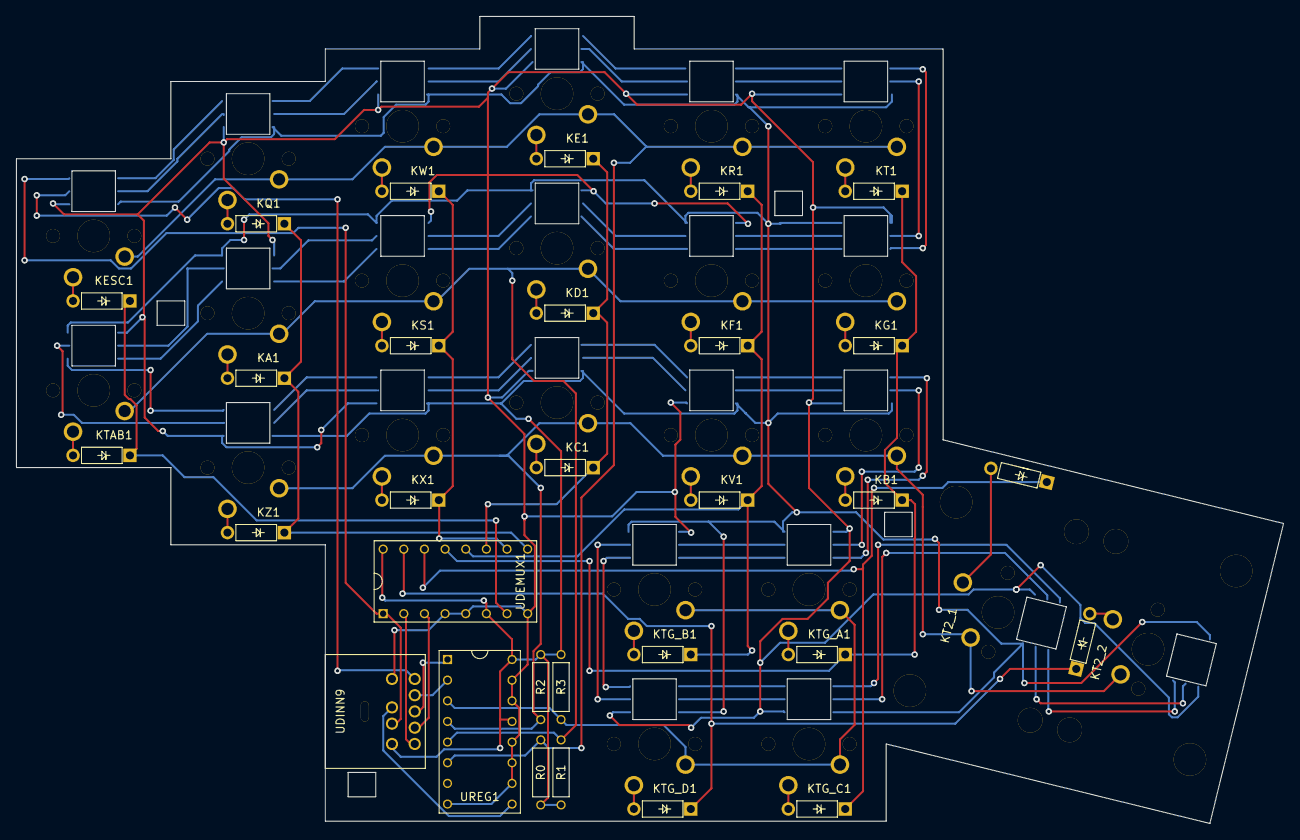
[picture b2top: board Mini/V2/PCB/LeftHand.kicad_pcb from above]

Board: 2 copper layers, 155.9 x 99.3 mm, 30 parts (0 on the bottom side), 88 nets.
